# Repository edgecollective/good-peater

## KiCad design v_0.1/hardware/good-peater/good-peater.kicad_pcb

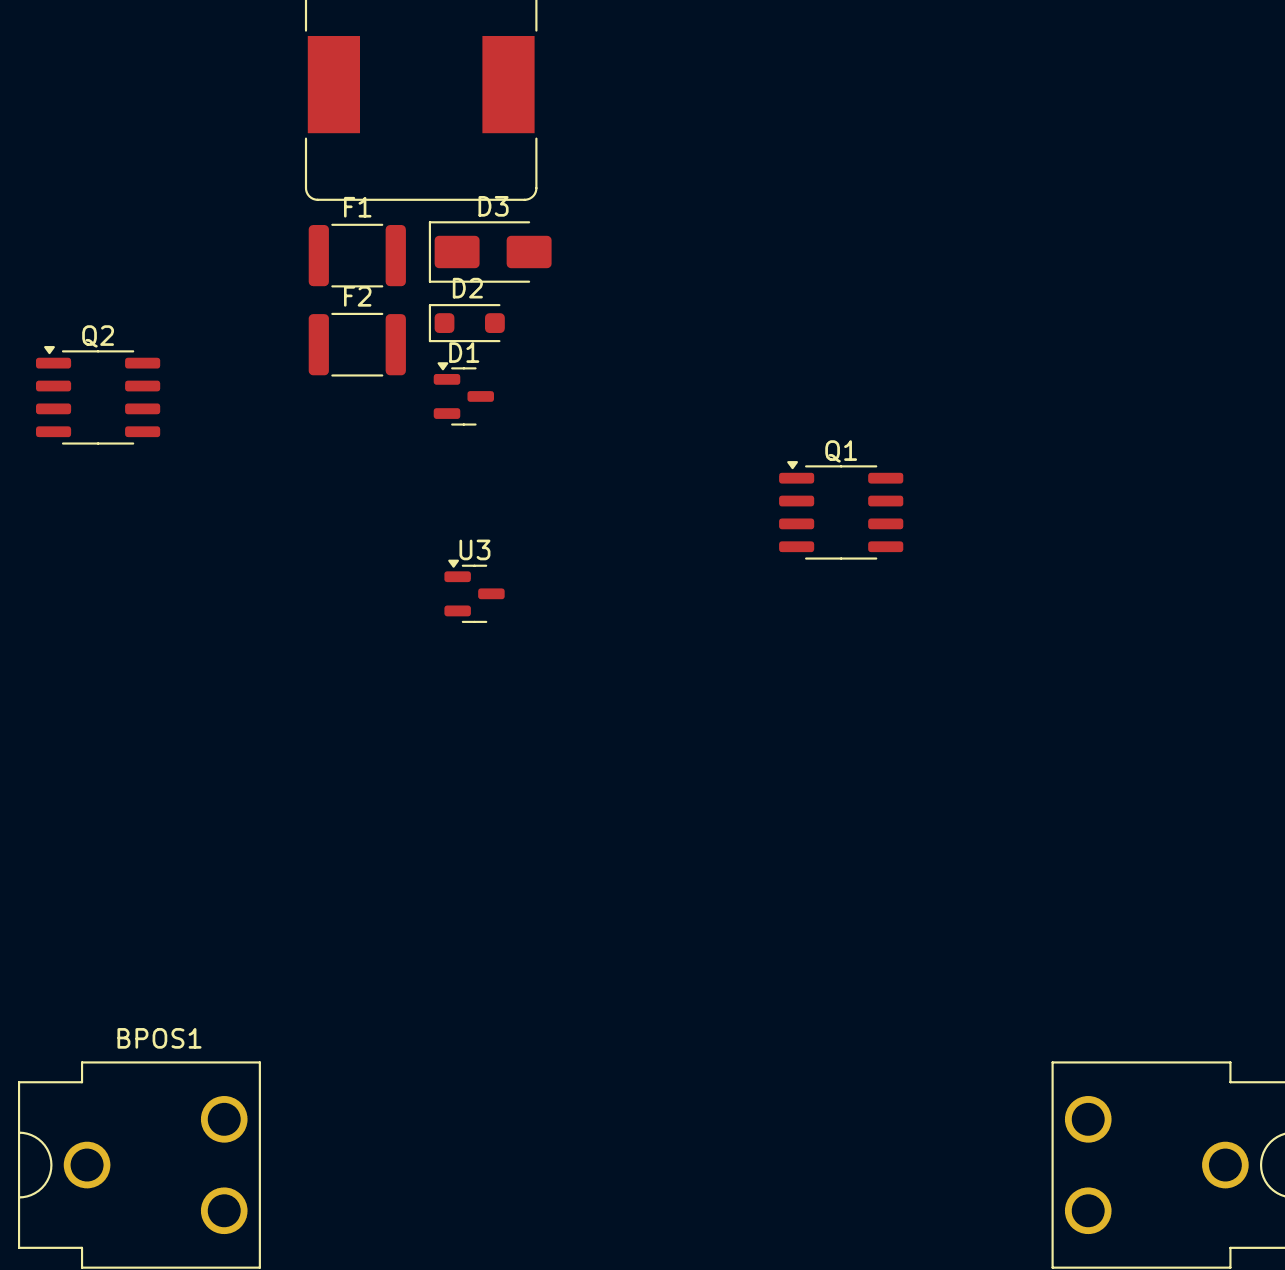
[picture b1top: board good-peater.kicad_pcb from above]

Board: 2 copper layers, 11 parts (0 on the bottom side), 4 nets, no tracks yet.

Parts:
BNEG1: BatteryClip_Keystone_54_D16-19mm
BPOS1: BatteryClip_Keystone_54_D16-19mm
D1: BAT54A; SOT-23
D2: BZT52C3V9 3.9V; D_SOD-123F
D3: SS54 (40V 5A); D_SMA
F1, F2: 0ZCG0110CF2B; Fuse_1812_4532Metric
L1: 47 uH; L_Bourns_SRR1260
Q1: FDS9435A; SOIC-8_3.9x4.9mm_P1.27mm
Q2: FDS6675BZ; SOIC-8_3.9x4.9mm_P1.27mm
U3: TCM810; SOT-23

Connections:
unnamed: Q1.5 (D), Q1.6 (D), Q1.7 (D), Q1.8 (D)
unnamed: Q1.1 (S), Q1.2 (S), Q1.3 (S)
unnamed: Q2.5 (D), Q2.6 (D), Q2.7 (D), Q2.8 (D)
unnamed: Q2.1 (S), Q2.2 (S), Q2.3 (S)
